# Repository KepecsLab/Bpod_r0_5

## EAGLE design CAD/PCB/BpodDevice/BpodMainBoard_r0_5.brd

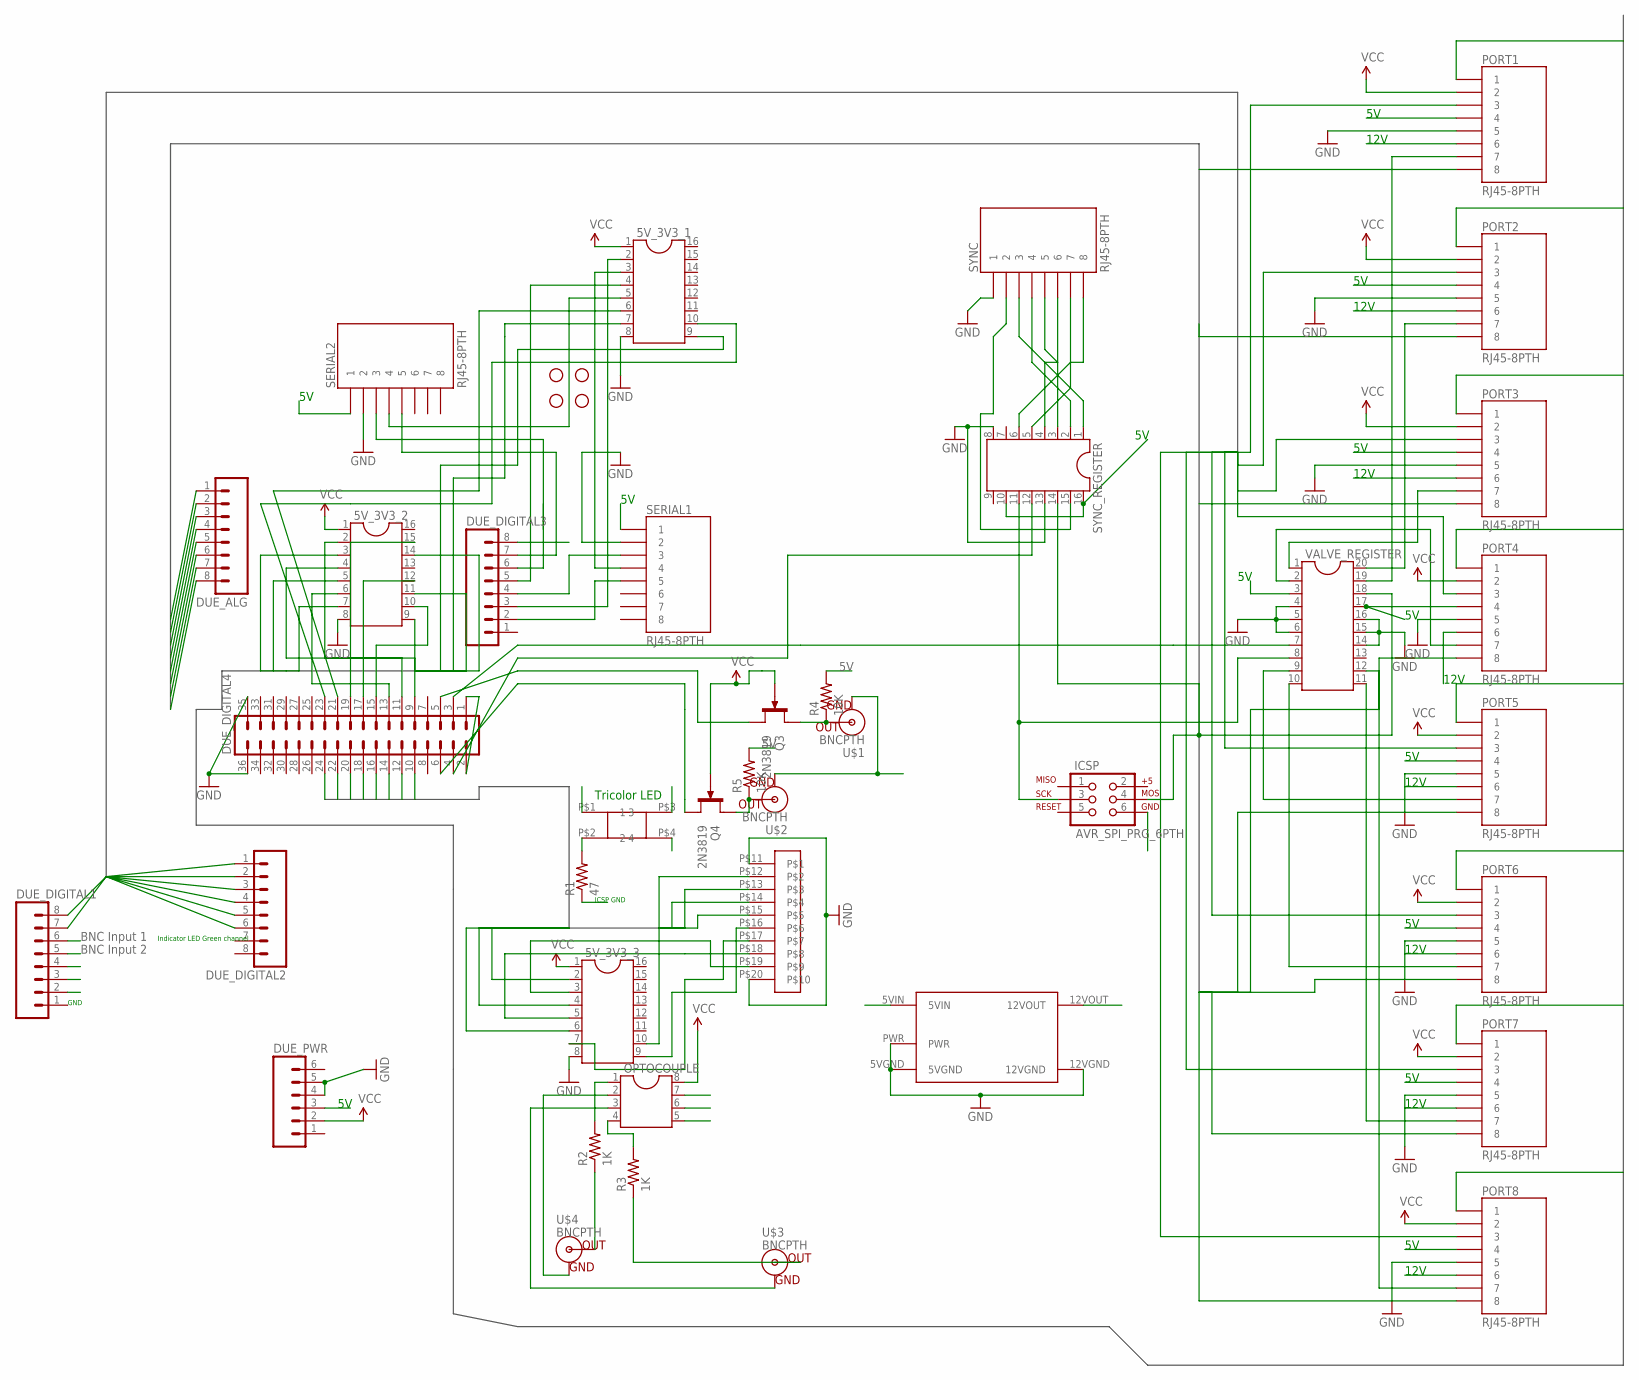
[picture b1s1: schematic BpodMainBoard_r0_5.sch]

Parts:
5V_3V3_1, 5V_3V3_2, 5V_3V3_3: DIL16
DUE_ALG: M081X08; 1X08
DUE_DIGITAL1, DUE_DIGITAL2, DUE_DIGITAL3: M081X08; 1X08
DUE_DIGITAL4: MA18-2
DUE_PWR: M06SIP; 1X06
ICSP: AVR_SPI_PRG_6PTH; 2X3
JP1, JP2, JP3, JP4: STAND-OFF
OPTOCOUPLE: DIL8; DIL08
PORT1, PORT2, PORT3, PORT4, PORT5, PORT6, PORT7, PORT8: RJ45-8PTH; RJ45-8
Q3, Q4: 2N3819; TO92F
R1: 47; AXIAL-0.3
R2, R3: 1K; AXIAL-0.3
R4, R5: 10K; AXIAL-0.3
SERIAL1, SERIAL2: RJ45-8PTH; RJ45-8
SYNC: RJ45-8PTH; RJ45-8
SYNC_REGISTER: DIL16
U$1, U$2, U$3, U$4: BNCPTH; BNC
U$5: TDK_LAMBDA_5V_TO_12V; TDK_LAMBDA_5V_12V
U$6: 10POS_SPRING_TERMINAL; 10POS_SCREW_TERMINAL
U$8: SQUARE_TRICOLOR_LED
VALVE_REGISTER: DIL20

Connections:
5V: DUE_DIGITAL4.1, DUE_DIGITAL4.2, DUE_PWR.3, PORT1.4, PORT2.4, PORT3.4, PORT4.4, PORT5.4, PORT6.4, PORT7.4, PORT8.4, R4.P$2 (2), R5.P$2 (2), SERIAL1.1, SERIAL2.1, SYNC_REGISTER.10, SYNC_REGISTER.16, U$5.5VIN, VALVE_REGISTER.3, VALVE_REGISTER.17
12V: PORT1.6, PORT2.6, PORT3.6, PORT4.6, PORT5.6, PORT6.6, PORT7.6, PORT8.6, U$5.12VOUT
ANALOG_BUS1: DUE_ALG.1, PORT1.8
ANALOG_BUS2: DUE_ALG.2, PORT2.8
ANALOG_BUS3: DUE_ALG.3, PORT3.8
ANALOG_BUS4: DUE_ALG.4, PORT4.8
ANALOG_BUS5: DUE_ALG.5, PORT5.8
ANALOG_BUS6: DUE_ALG.6, PORT6.8
ANALOG_BUS7: DUE_ALG.7, PORT7.8
ANALOG_BUS8: DUE_ALG.8, PORT8.8
BNCIN1: DUE_DIGITAL1.6, OPTOCOUPLE.7
BNCIN2: DUE_DIGITAL1.5, OPTOCOUPLE.6
DIGITAL_BUS1: 5V_3V3_2.3, PORT1.1
DIGITAL_BUS2: 5V_3V3_2.5, PORT2.1
DIGITAL_BUS3: 5V_3V3_2.7, PORT3.1
DIGITAL_BUS4: 5V_3V3_2.9, PORT4.1
DIGITAL_BUS5: 5V_3V3_2.11, PORT5.1
DIGITAL_BUS6: 5V_3V3_2.14, PORT6.1
DIGITAL_BUS7: 5V_3V3_1.7, PORT7.1
DIGITAL_BUS8: 5V_3V3_1.9, PORT8.1
DSUB_BUS1: 5V_3V3_3.2, DUE_DIGITAL4.10
DSUB_BUS2: 5V_3V3_3.4, DUE_DIGITAL4.12
DSUB_BUS3: 5V_3V3_3.6, DUE_DIGITAL4.14
DSUB_BUS4: 5V_3V3_3.10, DUE_DIGITAL4.16
DSUB_BUS5: DUE_DIGITAL4.18, U$6.P$15
DSUB_BUS6: DUE_DIGITAL4.20, U$6.P$14
DSUB_BUS7: DUE_DIGITAL4.22, U$6.P$13
DSUB_BUS8: DUE_DIGITAL4.24, U$6.P$12
GND: 5V_3V3_1.8, 5V_3V3_2.8, 5V_3V3_3.8, DUE_DIGITAL4.35, DUE_DIGITAL4.36, DUE_PWR.4, DUE_PWR.5, PORT1.5, PORT2.5, PORT3.5, PORT4.5, PORT5.5, PORT6.5, PORT7.5, PORT8.5, SERIAL1.2, SERIAL2.2, SYNC.1, SYNC_REGISTER.8, SYNC_REGISTER.13, U$5.5VGND, U$5.12VGND, U$5.PWR, U$6.P$11, U$6.P$20, VALVE_REGISTER.4, VALVE_REGISTER.5, VALVE_REGISTER.6, VALVE_REGISTER.14, VALVE_REGISTER.15, VALVE_REGISTER.16
ICSP_GND: ICSP.6, R1.P$1 (1)
LED1: DUE_DIGITAL1.4, U$8.P$3 (3)
LED2: DUE_DIGITAL1.3, U$8.P$4 (4)
LED3: DUE_DIGITAL3.8, U$8.P$1 (1)
LED_BUS1: DUE_DIGITAL1.7, PORT1.3
LED_BUS2: DUE_DIGITAL1.8, PORT2.3
LED_BUS3: DUE_DIGITAL2.1, PORT3.3
LED_BUS4: DUE_DIGITAL2.2, PORT4.3
LED_BUS5: DUE_DIGITAL2.3, PORT5.3
LED_BUS6: DUE_DIGITAL2.4, PORT6.3
LED_BUS7: DUE_DIGITAL2.5, PORT7.3
LED_BUS8: DUE_DIGITAL2.6, PORT8.3
unnamed: R2.P$1 (1), U$4.S (OUT)
unnamed: R3.P$1 (1), U$3.S (OUT)
unnamed: OPTOCOUPLE.1, R2.P$2 (2)
unnamed: OPTOCOUPLE.4, R3.P$2 (2)
unnamed: OPTOCOUPLE.2, U$4.GND
unnamed: OPTOCOUPLE.3, U$3.GND
unnamed: Q3.D, R4.P$1 (1), U$1.S (OUT)
unnamed: Q4.D, R5.P$1 (1), U$2.S (OUT)
unnamed: PORT1.7, VALVE_REGISTER.19
unnamed: PORT2.7, VALVE_REGISTER.20
unnamed: PORT3.7, VALVE_REGISTER.1
unnamed: PORT4.7, VALVE_REGISTER.2
unnamed: PORT5.7, VALVE_REGISTER.9
unnamed: PORT6.7, VALVE_REGISTER.10
unnamed: PORT7.7, VALVE_REGISTER.11
unnamed: PORT8.7, VALVE_REGISTER.12
unnamed: SYNC.2, SYNC_REGISTER.15
unnamed: SYNC.3, SYNC_REGISTER.1
unnamed: SYNC.4, SYNC_REGISTER.2
unnamed: DUE_DIGITAL4.3, VALVE_REGISTER.7
unnamed: SYNC.5, SYNC_REGISTER.3
unnamed: SYNC.6, SYNC_REGISTER.4
unnamed: SYNC.7, SYNC_REGISTER.5
unnamed: SYNC.8, SYNC_REGISTER.6
unnamed: R1.P$2 (2), U$8.P$2 (2)
unnamed: DUE_DIGITAL4.5, Q3.S
unnamed: DUE_DIGITAL4.4, SYNC_REGISTER.12
unnamed: DUE_DIGITAL4.6, Q4.S
unnamed: 5V_3V3_1.3, SERIAL1.4
unnamed: 5V_3V3_1.2, DUE_DIGITAL3.3
unnamed: DUE_DIGITAL3.4, SERIAL1.3
unnamed: 5V_3V3_1.5, SERIAL2.4
unnamed: 5V_3V3_1.4, DUE_DIGITAL3.5
unnamed: DUE_DIGITAL3.2, SERIAL1.5
unnamed: 5V_3V3_1.6, DUE_DIGITAL4.21
unnamed: DUE_DIGITAL3.6, SERIAL2.3
unnamed: 5V_3V3_1.10, DUE_DIGITAL4.23
unnamed: DUE_DIGITAL3.7, SERIAL2.5
unnamed: 5V_3V3_2.2, DUE_DIGITAL4.9
unnamed: 5V_3V3_2.4, DUE_DIGITAL4.11
unnamed: 5V_3V3_2.6, DUE_DIGITAL4.13
unnamed: 5V_3V3_2.10, DUE_DIGITAL4.15
unnamed: 5V_3V3_2.12, DUE_DIGITAL4.17
unnamed: 5V_3V3_2.15, DUE_DIGITAL4.19
unnamed: 5V_3V3_3.3, U$6.P$19
unnamed: 5V_3V3_3.5, U$6.P$18
unnamed: 5V_3V3_3.7, U$6.P$17
unnamed: 5V_3V3_3.9, U$6.P$16
SPI_CLK: ICSP.3, SYNC_REGISTER.11, VALVE_REGISTER.8
SPI_DATA: ICSP.4, SYNC_REGISTER.14, VALVE_REGISTER.18
UPPER_GND: DUE_DIGITAL1.2, OPTOCOUPLE.5, U$1.GND, U$2.GND
VCC: 5V_3V3_1.1, 5V_3V3_2.1, 5V_3V3_3.1, DUE_PWR.2, OPTOCOUPLE.8, PORT1.2, PORT2.2, PORT3.2, PORT4.2, PORT5.2, PORT6.2, PORT7.2, PORT8.2, Q3.G, Q4.G

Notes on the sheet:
12V
BNC Input 1
BNC Input 2
Indicator LED Green channel
Tricolor LED
ICSP GND
GND

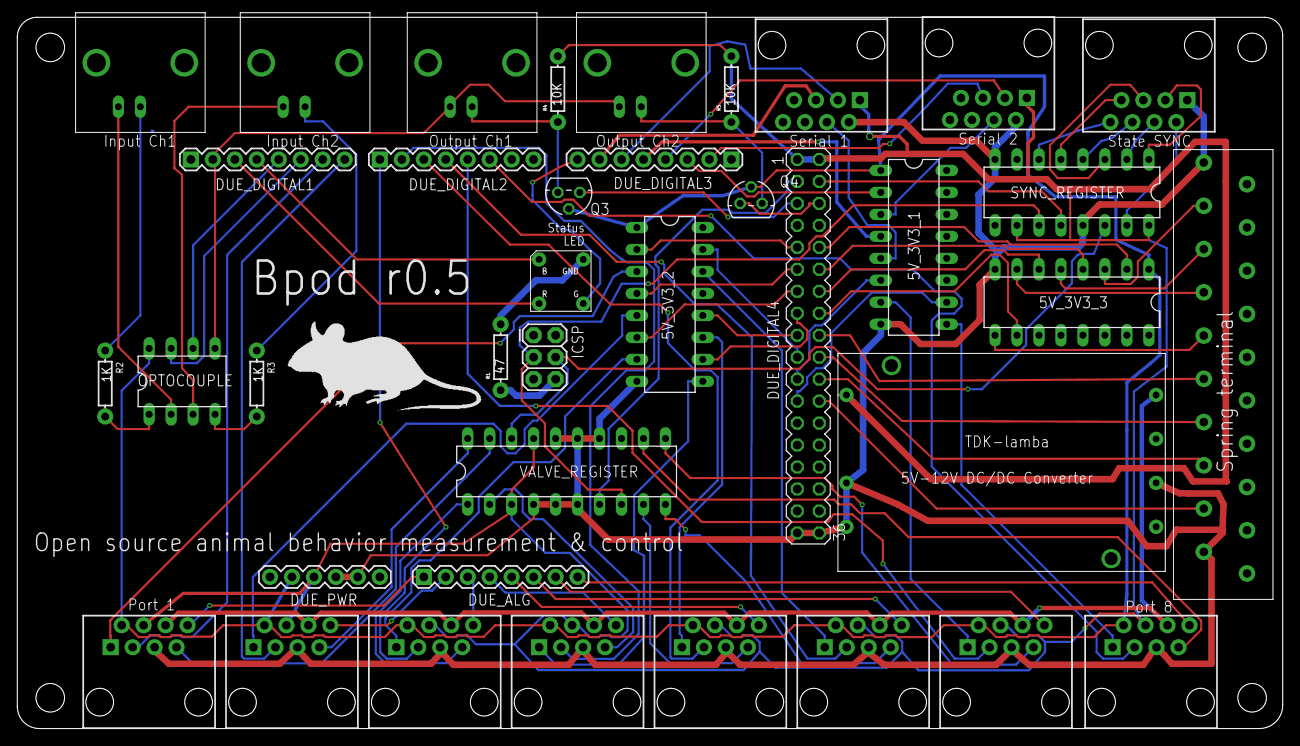
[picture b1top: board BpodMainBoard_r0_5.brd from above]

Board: 2 copper layers, 146.3 x 82.2 mm, 43 parts (0 on the bottom side), 93 nets.

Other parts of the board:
U$7: MOUSELOGO

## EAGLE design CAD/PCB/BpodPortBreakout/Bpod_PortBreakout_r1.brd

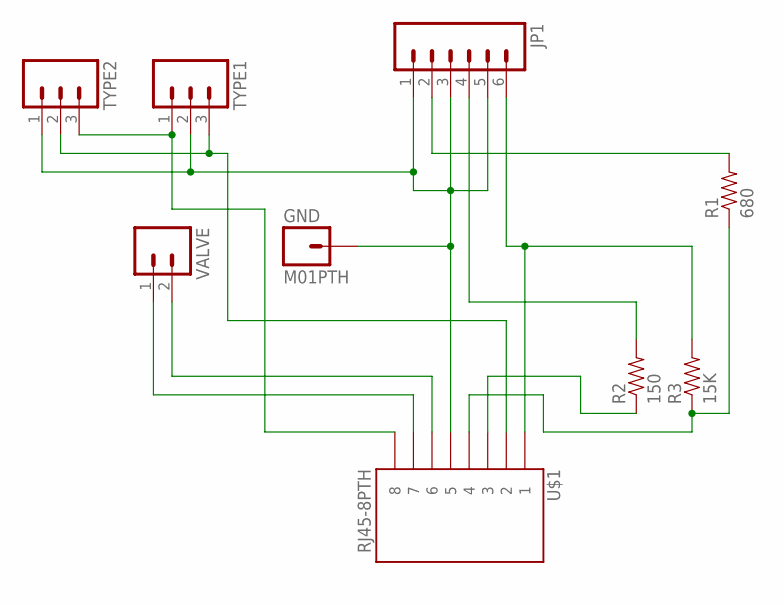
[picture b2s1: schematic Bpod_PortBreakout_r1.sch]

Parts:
GND: M01PTH; 1X01
JP1: M063.5MM-6; SCREWTERMINAL-3.5MM-6
R1: 680; AXIAL-0.4
R2: 150; AXIAL-0.4
R3: 15K; AXIAL-0.4
TYPE1, TYPE2: M03PTH; 1X03
U$1: RJ45-8PTH; RJ45-8
VALVE: M023.5MM_LOCK; SCREWTERMINAL-3.5MM-2_LOCK

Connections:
unnamed: JP1.6, R3.P$2 (2), U$1.1
unnamed: R1.P$1 (1), R3.P$1 (1), U$1.4
unnamed: JP1.2, R1.P$2 (2)
unnamed: GND.1, JP1.1, JP1.3, JP1.5, TYPE1.2, TYPE2.1, U$1.5
unnamed: U$1.6, VALVE.2
unnamed: U$1.7, VALVE.1
unnamed: JP1.4, R2.P$2 (2)
unnamed: R2.P$1 (1), U$1.3
unnamed: TYPE1.3, TYPE2.2, U$1.2
unnamed: TYPE1.1, TYPE2.3, U$1.8

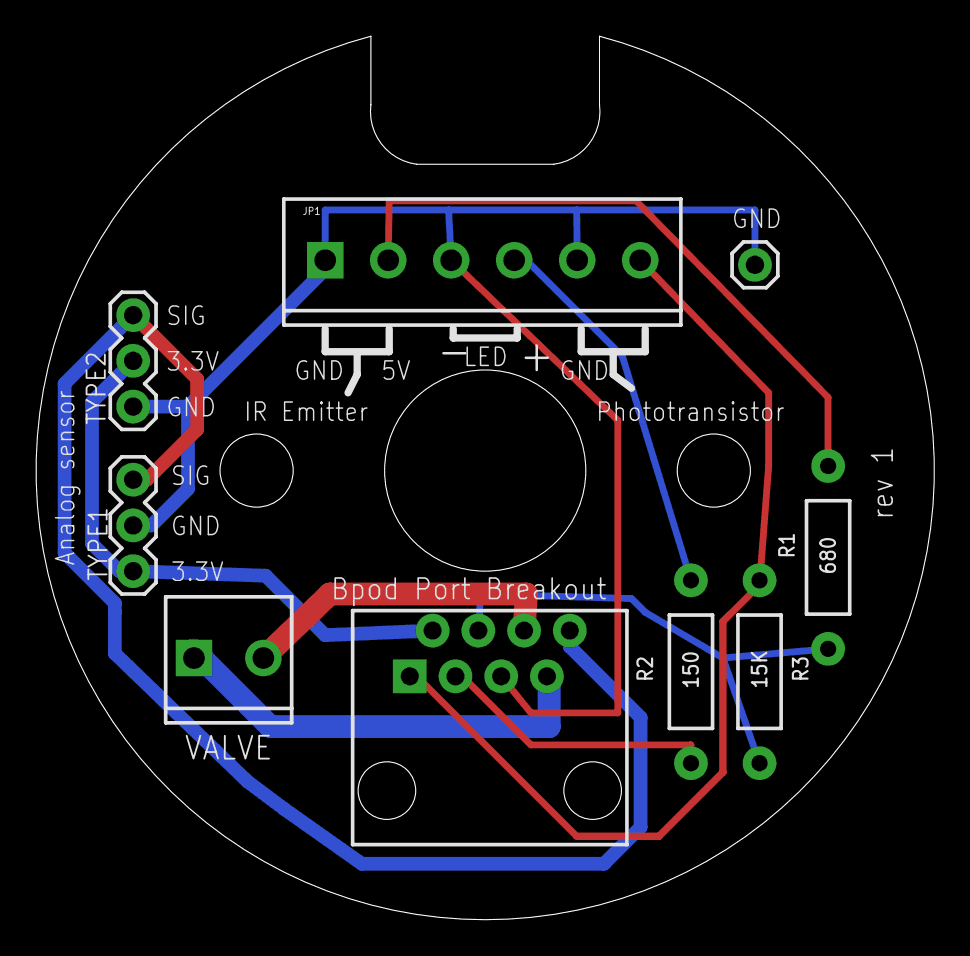
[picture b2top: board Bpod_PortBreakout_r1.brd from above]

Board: 4 copper layers, 49.9 x 49.1 mm, 9 parts (0 on the bottom side), 10 nets.

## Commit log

2013-12-30 Empty commit for future use
2014-03-31 Actual initial commit
2014-04-15 Removed redundant setting of serial port defaults in InitializeHardware Fixed bug in sending single state matrix
2014-07-01 Major update: -Integrates with PsychToolbox (if installed) for low latency serial and possible future use as a sound server -Adds sound support with Teensy Audio board, added as a hardware serial dev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
2014-07-28 -Integrated Bpod with PsychToolbox serial interface (if detected) for low latency -Added interface for closed loop feedback plugins, and an example plugin: a sound server using ASIO and PsychToolbox,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
2014-08-07 - Fixed latency issue with PsychToolbox sound server. Sound latency ranges from 6-8ms for stereo 192kHz sound with Ubuntu 14.04 and MATLAB r2011a - Changed positions of plugin figures so they don't g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
2014-08-26 -Fixed bug with override command (crashed if used prior to uploading a state matrix) -Updated PCB design to eliminate a stray trace (did not affect function of prior revision)
2014-08-26 -Turned off saved data compression (slightly reduces inter trial interval if saving) -Set PsychToolbox sound server to use only channels 1-4; 1-2 = L,R Stereo. 3-4 = sync pulse.
2014-08-27 -Fixes PsychToolbox sound server plugin for use with Xonar DX on Ubuntu, with expected channel mappings. Some systems may be mismatched so that front L&R are played on a different plug on the sound c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
2014-10-13 -Added license information to each code file -Added a hardware serial Ethernet client and firmware (to send text strings via Ethernet from the state machine using Arduino Leonardo + Bpod shield + Ard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
2014-11-01 -Updated firmware to fix 2 bugs: >After configuring low impedence inputs from the settings menu, Bpod would not return the unused channel status to 0, resulting in false events on the disconnected ch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
2014-11-02 -Optimized BpodNotebook plugin for speed -Optimized ParameterGUI plugin for speed -Optimized OutcomePlot plugin for speed -Optimized AddTrialEvents for speed -Optimized liquid calibration and lookup 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
2014-11-03 Fixed a bug - on actual hardware (not emulator), Bpod now properly exits state matrix loop when the user manually ends the protocol.
2014-11-14 Performance improvements: -Bpod now generates a blank state matrix on initialization and stores it in memory, so it doesn't have to be generated on each call to NewStateMatrix. -Improvements in RunSt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
2014-11-14 -Changed timer display on Bpod console - now shows trial start time (instead of "protocol time". -Removed parser from AddState - now all argument pairs must be listed in order (for efficiency) -Added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
2014-12-26 Added Bpod / Neuralynx sync adapter PCB design (tested) Removed outdated enclosure design files
2015-03-13 -Added play/pause function. One line must be added to each protocol: HandlePauseCondition; (See example protocols for placement) -Added help button link to Wiki -Bug fixes for liquid calibration unde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
2015-06-29 -Fixed stereo sounds in Bpod emulator sound server -Added a new plugin for visualizing outcomes of non-sided tasks -Added support for triggering state changes from Bonsai -Fixed soft-code manual over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
2015-06-29 Fixed SoundSamp protocol (had been hacked locally)
2015-06-29 Deleted an ASV
2015-07-06 Added design for mousebox port interface board. Updated native graphics package
2016-07-20 wavread not supported in r2016, now audioread

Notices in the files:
parts and their libraries:
SparkFun-Passives: Licensing: CC v3.0 Share-Alike You are welcome to use this library for commercial purposes.
